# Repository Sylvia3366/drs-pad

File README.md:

# DRS-Pad 🏎️💨

[ONSHAPE CAD](https://cad.onshape.com/documents/f871e0d794d92113bb05b77c/w/53d91f0d4610f412f5f57ae5/e/b5381f3e555c04c2681f8eeb?renderMode=0&uiState=6a35e3a11d4e4c91f8bc6b19)
-

What is it? 
-
The DRS-Pad, or Desktop Response System Pad, is a macropad powered by the XIAO-ESP32-S3 with 9 mechanical keys to save your fingers and hasten your workflow so you can be more efficient! Named after the now retired DRS (Drag Reduction System, RIP 2011–2025), the DRS-Pad is modeled after the iconic F1 Pirelli tire (specifically the soft one). Paired with a 1.14" IPS LCD display, it allows you to view race/qualifying results on race/qualification days and WDC/WCC standings on non-race days.

Why did I make it? 
-
First and foremost, I've been wanting to make a macropad for the longest time now. I'm someone who's constantly on my computer—whether it be writing stories, programming/playing games, editing videos, or just doing homework, my fingers are constantly jumping around my keyboard. As a result, I often end the day with cramped fingers, so hopefully, this macropad will solve that :(

As for the theme: I've been an F1 fan for some time now, and I've grown a habit of checking my phone and social media for race updates. But I simply can't do that when I'm in the middle of working on CADing or programming. So I thought, what if I could combine both those problems into one solution?

How does it work?
-
So I made the DRS-Pad! Aside from being your usual, run-of-the-mill macropad for improving workflow and allowing your fingers to rest, there's a little screen that updates you on the latest F1 standings in real time! On a typical, non-race or quali day, the DRS-Pad will flicker between the WDC (driver's championship) and WCC (constructor's championship) every minute. During free practice, quali, and race days, the screen will update every minute with live feed on the current event, displaying the top 9 drivers. This is done through using an open source API **(https://openf1.org)**.

Now, you can save your fingers AND enjoy some nice F1 updates all at the same time :)!

# Designing the PCB 🏁
PCB designed on KiCAD!
-

CADed and assembled on OnShape!
-

Rendered on Fusion360!
-

# Bill of Materials 🧾
| Name | Qty | Unit | Price (USD) | Total (USD) | MOQ | MOQ Price | Source |
| :--- | :---: | :---: | ---: | ---: | ---: | ---: | :--- |
| Seeed Studio XIAO ESP32 S3 | 1 | pcs | 9.46 | 9.46 | 1 | 9.46 | [Link](https://www.aliexpress.us/item/3256808047100037.html) |
| 1.14 inch IPS LCD 135x240 | 1 | pcs | 2.72 | 2.72 | 1 | 2.72 | [Link](https://www.aliexpress.us/item/3256808427301455.html) |
| 1N4148 SOD-123 Diode | 9 | pcs | 0.04 | 0.33 | 100 | 3.70 | [Link](https://www.aliexpress.us/item/3256806021629352.html) |
| Cherry MX Switch | 9 | pcs | 0.77 | 6.95 | 10 | 7.72 | [Link](https://www.aliexpress.us/item/3256808812099705.html) |
| M2 4mm Screws | 4 | pcs | 0.03 | 0.12 | 50 | 1.51 | [Link](https://www.aliexpress.us/item/2251832785290389.html) |
| M2 14mm Screws | 4 | pcs | 0.04 | 0.14 | 50 | 1.75 | [Link](https://www.aliexpress.us/item/2251832785290389.html) |
| PCB | 1 | pcs | 0.80 | 0.80 | 5 | 4.00 | [Link](https://jlcpcb.com) |
| PLA 3D Printed Case | 1 | pcs | - | - | - | - |
| **Total** | **30** | **-** | **-** | **20.52** | **-** | **30.86** | **-** |

# Build and Assembly 🔧

Required Tools
-
1. Solder
2. Soldering iron
3. Tweezers
4. Screwdriver for M2 screws
5. Computer w. a USB port
6. 3D printer

Assembly
-
1. Attach the keycaps onto the switches.
2. Solder the 1N4148 diodes onto the PCB.
3. Solder the remaining parts onto the PCB.
4. Place the assembled PCB into the bottom case.
5. Secure on the mounting holes with M2 4mm screws.
6. Secure the top case on the screw holes with M2 14mm screws (I used 12mm in the CAD, which works).
7. Use Arduino IDE for the firmware.
8. Connect the ESP32 to your computer via USB-C to upload code.
9. Upload firmware.
10. Make sure to change the WiFi so the network matches your own.
11. Test the OLED display and keycaps.
12. Test live updates.

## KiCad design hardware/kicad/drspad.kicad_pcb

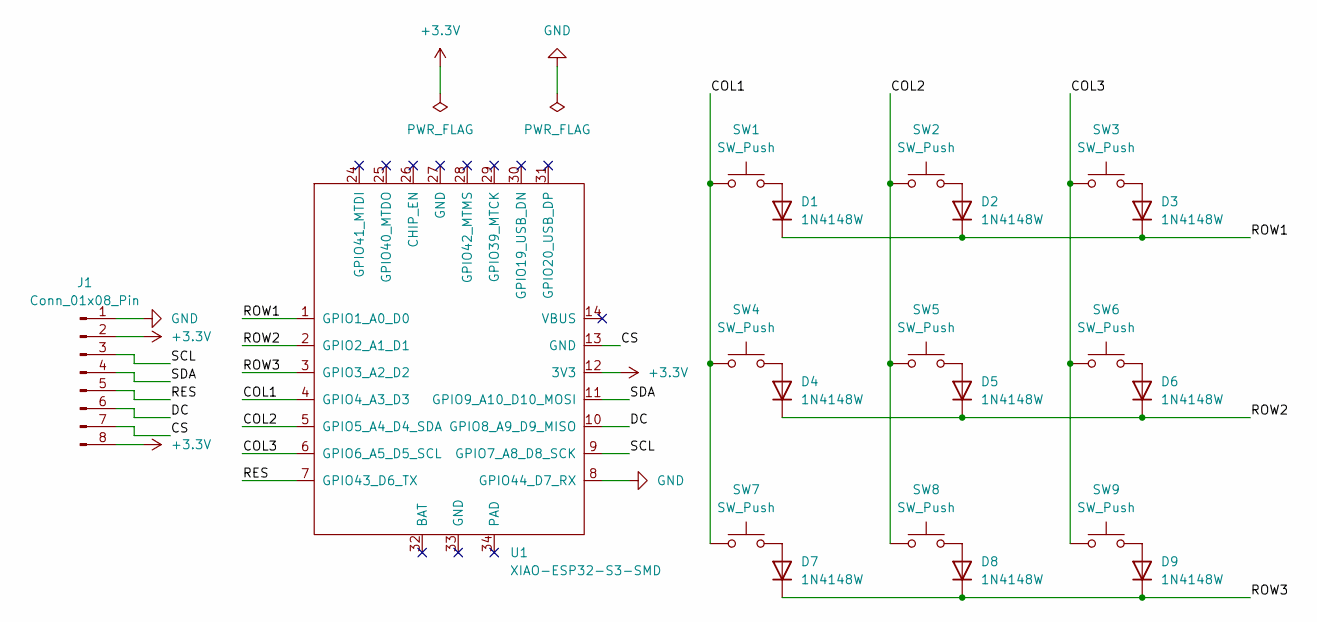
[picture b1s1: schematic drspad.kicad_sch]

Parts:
D1, D2, D3, D4, D5, D6, D7, D8, D9: 1N4148W; D_SOD-123
J1: Conn_01x08_Pin; PinHeader_1x08_P2.54mm_Vertical
SW1, SW2, SW3, SW4, SW5, SW6, SW7, SW8, SW9: SW_Push; SW_Cherry_MX_1.00u_PCB
U1: XIAO-ESP32-S3-SMD; XIAO-ESP32-S3-DIP

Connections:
+3.3V: J1.2, J1.8, U1.12 (3V3)
/COL1: SW1.1, SW4.1, SW7.1, U1.4 (GPIO4_A3_D3)
/COL2: SW2.1, SW5.1, SW8.1, U1.5 (GPIO5_A4_D4_SDA)
/COL3: SW3.1, SW6.1, SW9.1, U1.6 (GPIO6_A5_D5_SCL)
/CS: J1.7, U1.13 (GND)
/DC: J1.6, U1.10 (GPIO8_A9_D9_MISO)
/RES: J1.5, U1.7 (GPIO43_D6_TX)
/ROW1: D1.1 (K), D2.1 (K), D3.1 (K), U1.1 (GPIO1_A0_D0)
/ROW2: D4.1 (K), D5.1 (K), D6.1 (K), U1.2 (GPIO2_A1_D1)
/ROW3: D7.1 (K), D8.1 (K), D9.1 (K), U1.3 (GPIO3_A2_D2)
/SCL: J1.3, U1.9 (GPIO7_A8_D8_SCK)
/SDA: J1.4, U1.11 (GPIO9_A10_D10_MOSI)
GND: J1.1, U1.8 (GPIO44_D7_RX)
unnamed: D1.2 (A), SW1.2
unnamed: D2.2 (A), SW2.2
unnamed: D3.2 (A), SW3.2
unnamed: D4.2 (A), SW4.2
unnamed: D5.2 (A), SW5.2
unnamed: D6.2 (A), SW6.2
unnamed: D7.2 (A), SW7.2
unnamed: D8.2 (A), SW8.2
unnamed: D9.2 (A), SW9.2

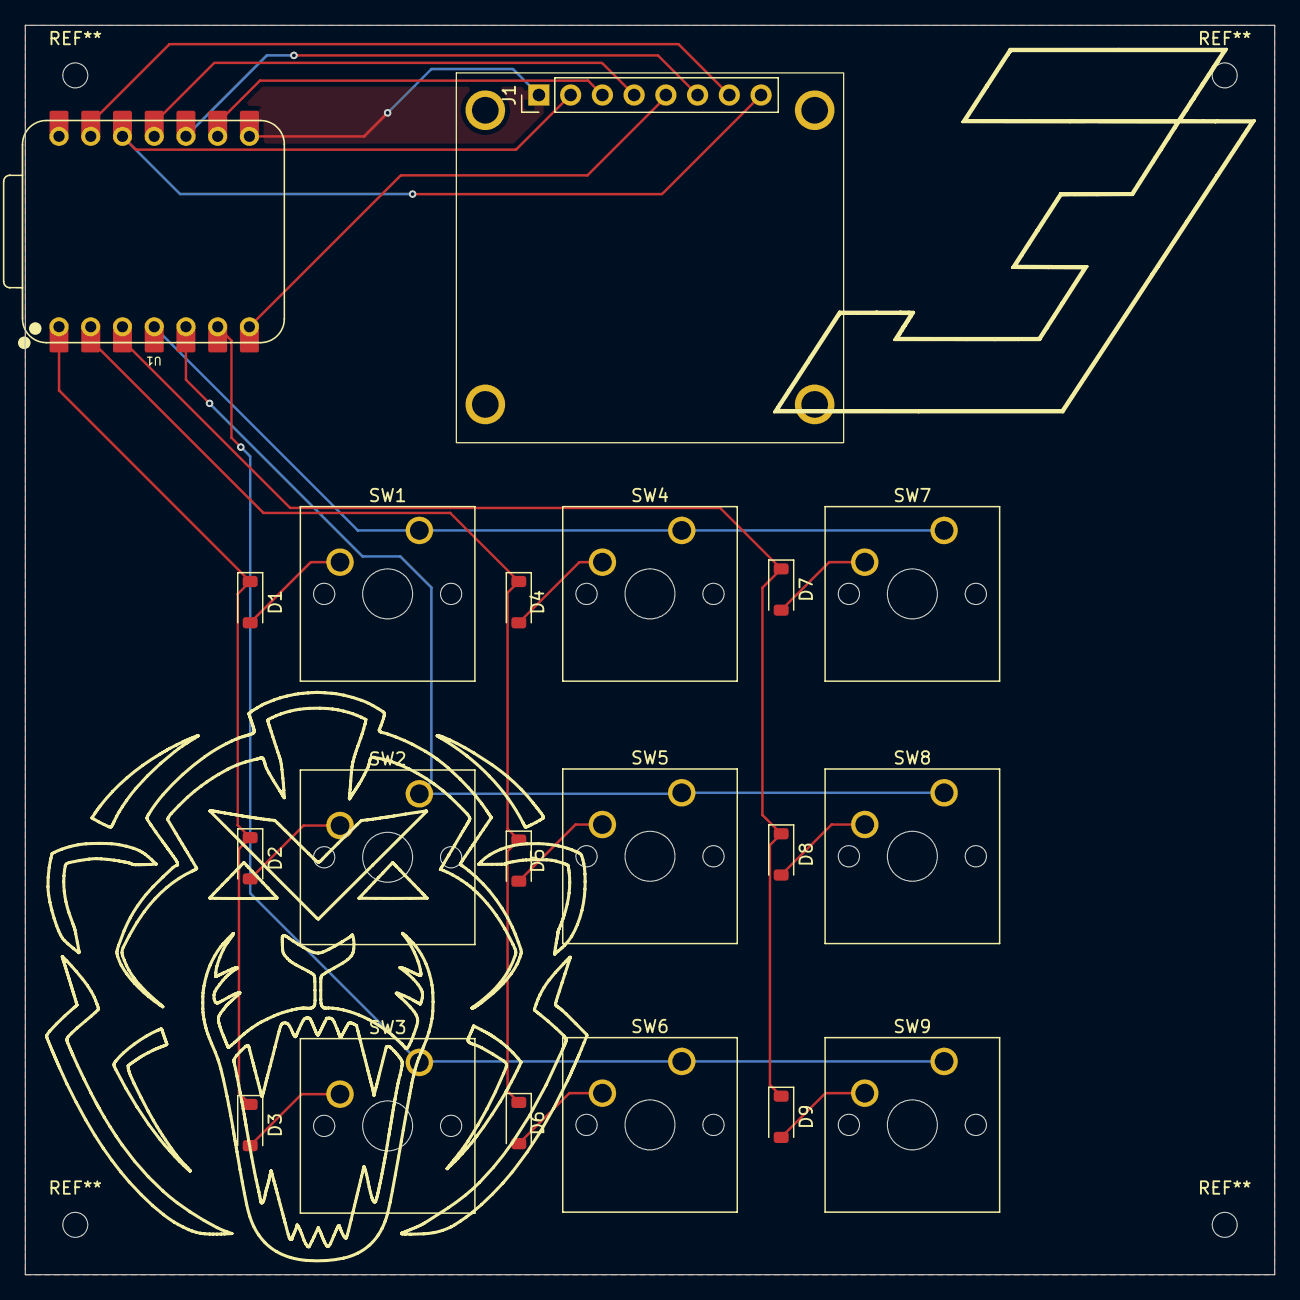
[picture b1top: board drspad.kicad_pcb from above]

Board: 2 copper layers, 100.0 x 100.0 mm, 20 parts (0 on the bottom side), 22 nets.

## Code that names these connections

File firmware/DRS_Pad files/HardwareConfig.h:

#ifndef HARDWARE_CONFIG_H
#define HARDWARE_CONFIG_H

#define TFT_MOSI 10
#define TFT_SCLK 7
#define TFT_DC 8
#define TFT_CS -1
#define TFT_RST 43

#define ROW1 1
#define ROW2 2
#define ROW3 3
#define COL1 4
#define COL2 5
#define COL3 6

const int rowPins[] = {1,2,3};
const int colPins[] = {4,5,6};

#endif

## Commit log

2026-06-20 Create hi
2026-06-20 Create i
2026-06-21 Create ho
